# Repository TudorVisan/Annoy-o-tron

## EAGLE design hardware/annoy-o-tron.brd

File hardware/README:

Complete BOM available at
https://docs.google.com/spreadsheets/d/16hriwUa0v_gi9K-n5bR37Sd7s5v-uVvUdp3O5QT6Rfs/edit#gid=0

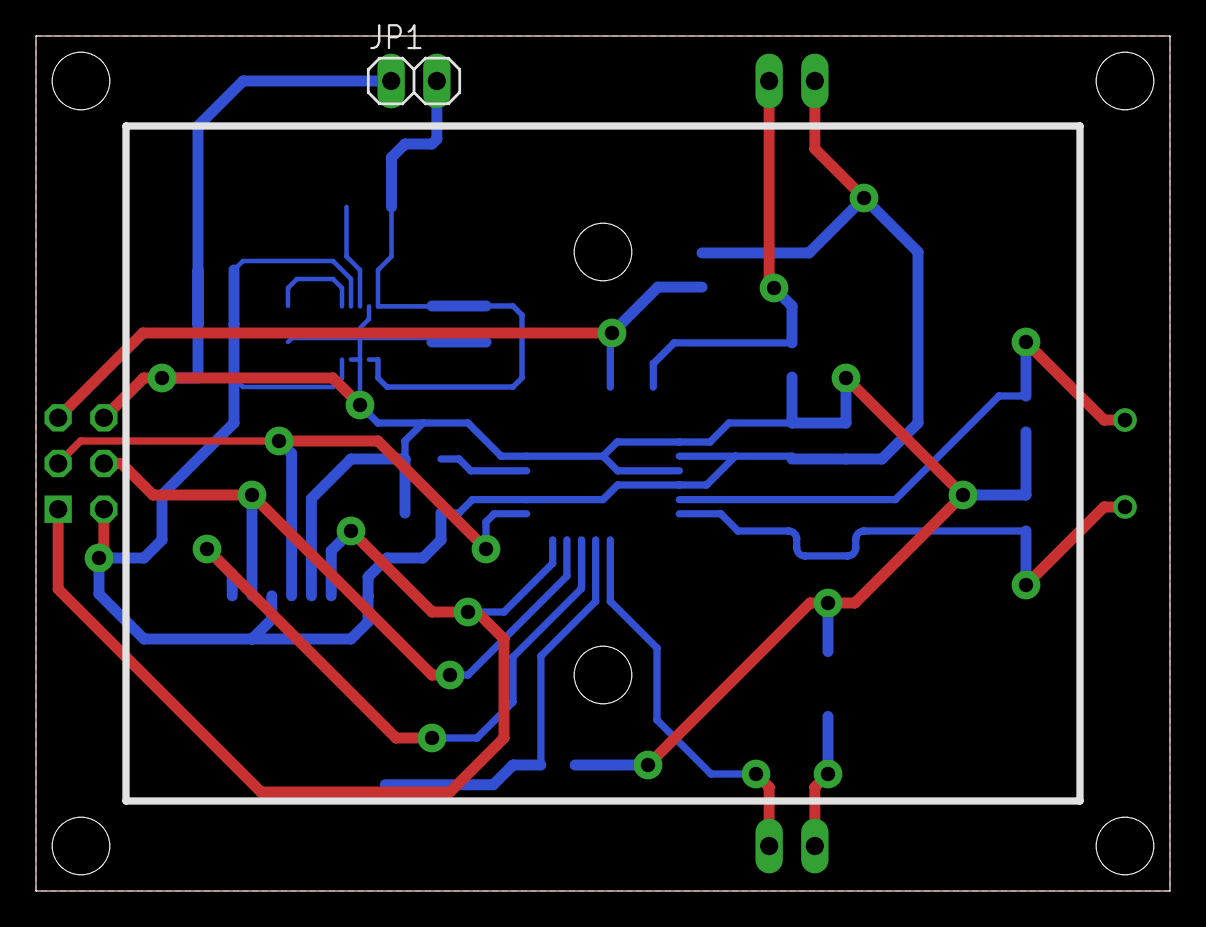
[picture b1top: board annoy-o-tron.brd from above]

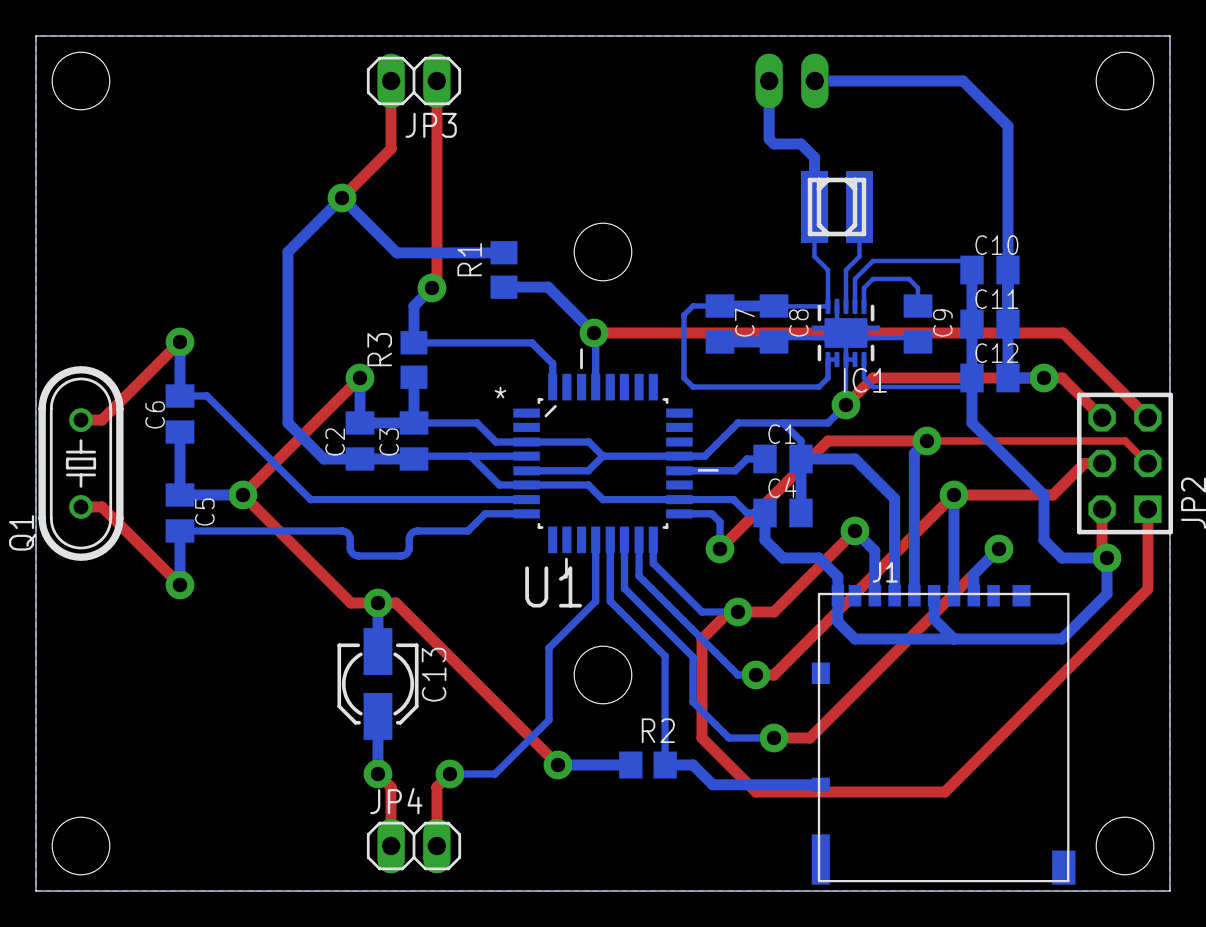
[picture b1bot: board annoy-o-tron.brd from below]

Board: 2 copper layers, 63.0 x 47.5 mm, 25 parts (24 on the bottom side), 17 nets.

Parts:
C1, C2, C3, C4, C8, C9, C12: 100nF; C0805K
C5, C6: 15pF; C0805K
C7, C10: 10uF; C0805K
C11: 1uF; C0805K
C13: 100uF; 153CLV-0405
IC1: TPS61201; S-PDSO-N10
J1: DM3AT-SF-PEJM5
JP1, JP3, JP4: 1X02
JP2: AVR-ISP-6VERT; AVR-ISP-6
L1: 2.2uH; SRN3012TA
Q1: 8MHz; HC49/S
R1, R2, R3: 10k; R0805
U1: ATMEGA328P-AU; QFP80P900X900X120-32N

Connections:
BUTTON: JP3.1, R3.2, U1.32
GND: C1.2, C2.2, C3.2, C4.2, C5.1, C6.1, C7.2, C8.2, C9.2, C10.2, C11.2, C12.2, C13.-, IC1.4, IC1.8, IC1.9, IC1.PP, IC1.PP@1, IC1.PP@2, J1.6, JP1.1, JP2.6, R2.1, R3.1, U1.3, U1.5, U1.21
INS: J1.A, R2.2, U1.13
MISO: J1.7, JP2.1, U1.16
MOSI: J1.3, JP2.4, U1.15
unnamed: IC1.3, L1.P$1
unnamed: C1.1, U1.20
unnamed: C9.1, IC1.1
unnamed: C13.+, JP4.1
RESET: JP2.5, R1.1, U1.29
SCK: J1.5, JP2.3, U1.17
SPKR: JP4.2, U1.12
SS: J1.2, U1.14
VCC: C2.1, C3.1, C4.1, C10.1, C11.1, C12.1, IC1.2, IC1.10, J1.4, J1.B, JP2.2, JP3.2, R1.2, U1.4, U1.6, U1.18
VCC/2: C7.1, C8.1, IC1.5, IC1.6, IC1.7, JP1.2, L1.P$2
XTAL1: C6.2, Q1.2, U1.7
XTAL2: C5.2, Q1.1, U1.8

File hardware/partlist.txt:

Partlist

Exported from annoy-o-tron.sch at 02/12/2016 10:35

EAGLE Version 7.7.0 Copyright (c) 1988-2016 CadSoft

Assembly variant: 

Part     Value          Device             Package               Library        Sheet

C1       100nF          C-EUC0805          C0805                 rcl            1
C2       100nF          C-EUC0805          C0805                 rcl            1
C3       100nF          C-EUC0805          C0805                 rcl            1
C4       100nF          C-EUC0805          C0805                 rcl            1
C5       15pF           C-EUC0805K         C0805K                rcl            1
C6       15pF           C-EUC0805K         C0805K                resistor       1
C7       10uF           C-EUC0805K         C0805K                resistor       1
C8       100nF          C-EUC0805K         C0805K                resistor       1
C9       100nF          C-EUC0805K         C0805K                resistor       1
C10      10uF           C-EUC0805K         C0805K                resistor       1
C11      1uF            C-EUC0805K         C0805K                resistor       1
C12      100nF          C-EUC0805K         C0805K                resistor       1
C13      100uF          CPOL-EU153CLV-0405 153CLV-0405           resistor       1
IC1      TPS61201       TPS61201           S-PDSO-N10            texas          1
J2       DM3AT-SF-PEJM5 DM3AT-SF-PEJM5     DM3AT-SF-PEJM5        DM3AT-SF-PEJM5 1
JP1                     PINHD-1X2          1X02                  pinhead        1
JP2      AVR-ISP-6VERT  AVR-ISP-6VERT      AVR-ISP-6             avr-7          1
JP3                     PINHD-1X2          1X02                  pinhead        1
JP4                     PINHD-1X2          1X02                  pinhead        1
L1       2.2uH          SRN3012TA          SRN3012TA             tudor          1
Q1       8MHz           CRYSTALHC49S       HC49/S                crystal        1
R1       10k            R-EU_R0805         R0805                 rcl            1
R2       10k            R-EU_R0805         R0805                 rcl            1
R3       10k            R-EU_R0805         R0805                 rcl            1
U3       ATMEGA328P-AU  ATMEGA328P-AU      QFP80P900X900X120-32N tudor          1

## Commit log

2016-12-06 Hello! Hello! Hello!
2016-12-06 Fixed for board.
2016-12-06 Replaced ATmega32-16 with ATmega328P. Replace TPS62201 with TPS61201, schematic stil unfinished.
2016-12-06 Added hardware and software.
2016-12-06 Removed generated files.
2016-12-06 Modifications to schematic. Finished board. Added part list and hardware README.
2016-12-06 Made capacitor packages uniform. Naming changes in schematic. Board corrections for new packages.
2016-12-06 Finished schematic.
2016-12-20 Added pdf and vim temporary files to be ignored.
